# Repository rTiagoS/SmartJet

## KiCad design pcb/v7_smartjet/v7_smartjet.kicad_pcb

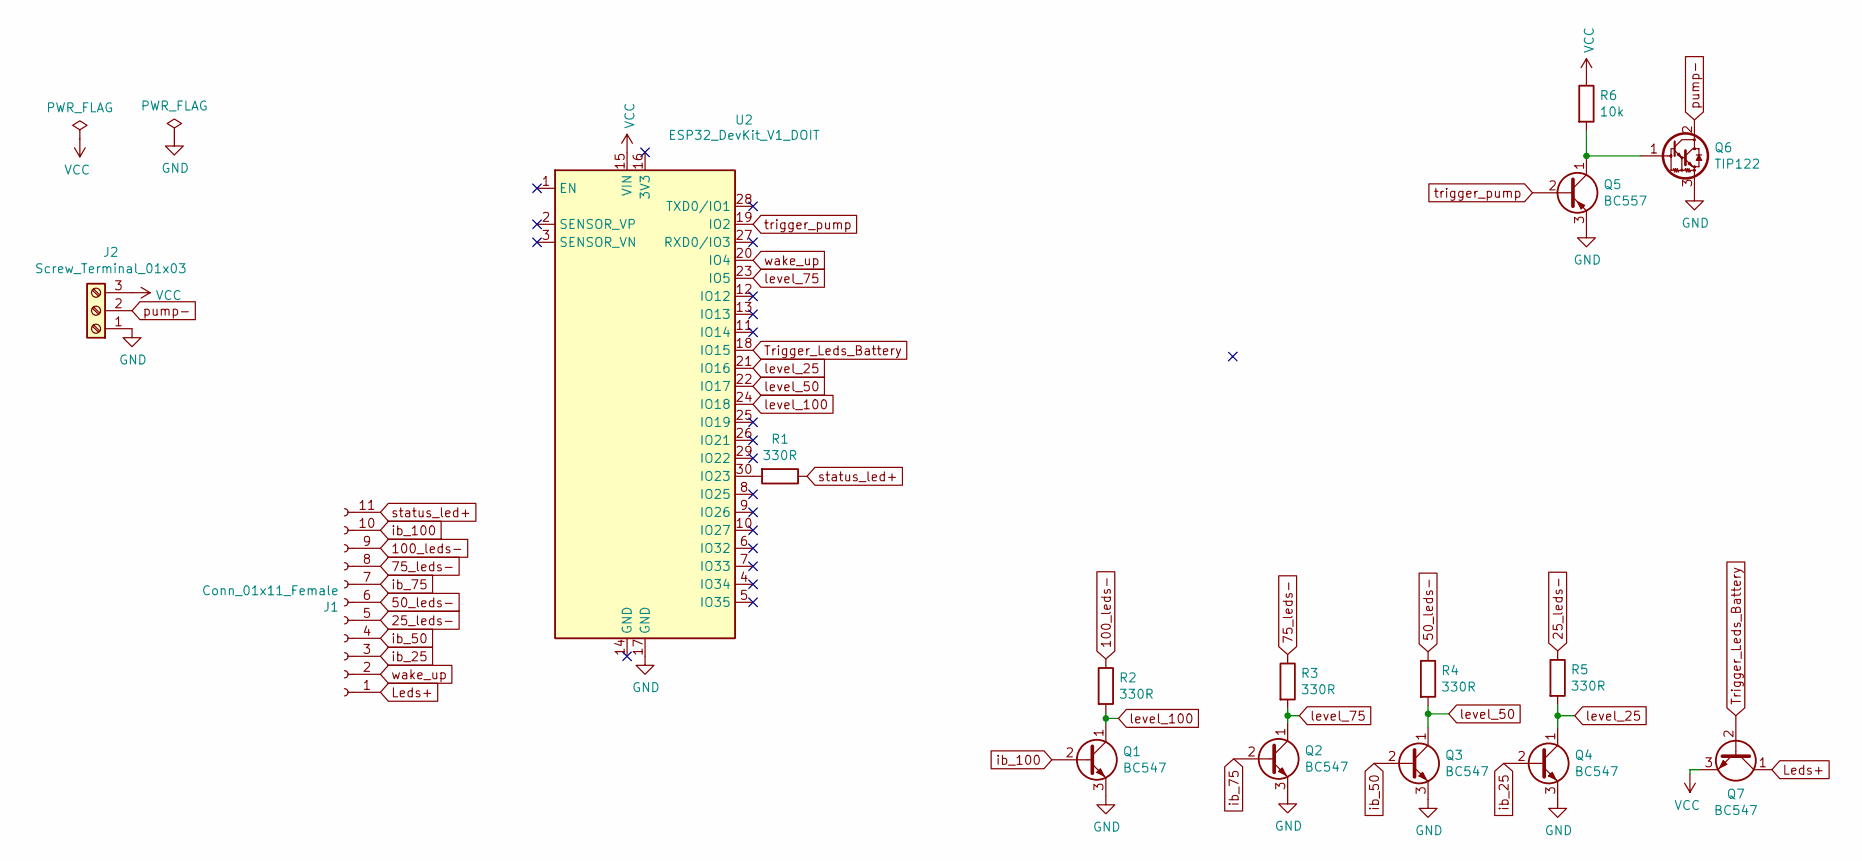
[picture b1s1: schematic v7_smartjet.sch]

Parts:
J1: Conn_01x11_Female; PinSocket_1x11_P2.54mm_Horizontal
J2: Screw_Terminal_01x03; TerminalBlock_bornier-3_P5.08mm
Q1, Q2, Q3, Q4, Q7: BC547; TO-92_Inline
Q5: BC557; TO-92_Inline
Q6: TIP122; TO-220-3_Vertical
R1, R2, R3, R4, R5: 330R; R_Axial_DIN0204_L3.6mm_D1.6mm_P7.62mm_Horizontal
R6: 10k; R_Axial_DIN0204_L3.6mm_D1.6mm_P7.62mm_Horizontal
U2: ESP32_DevKit_V1_DOIT; esp32_devkit_v1

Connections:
25_leds-: J1.5, R5.1
50_leds-: J1.6, R4.1
75_leds-: J1.8, R3.1
100_leds-: J1.9, R2.1
GND: J2.1, Q1.3 (E), Q2.3 (E), Q3.3 (E), Q4.3 (E), Q5.3 (E), Q6.3 (E), U2.17 (GND)
Leds+: J1.1, Q7.1 (C)
unnamed: Q5.1 (C), Q6.1 (B), R6.2
unnamed: R1.2, U2.30 (IO23)
Trigger_Leds_Battery: Q7.2 (B), U2.18 (IO15)
VCC: J2.3, Q7.3 (E), R6.1, U2.15 (VIN)
ib_25: J1.3, Q4.2 (B)
ib_50: J1.4, Q3.2 (B)
ib_75: J1.7, Q2.2 (B)
ib_100: J1.10, Q1.2 (B)
level_25: Q4.1 (C), R5.2, U2.21 (IO16)
level_50: Q3.1 (C), R4.2, U2.22 (IO17)
level_75: Q2.1 (C), R3.2, U2.23 (IO5)
level_100: Q1.1 (C), R2.2, U2.24 (IO18)
pump-: J2.2, Q6.2 (C)
status_led+: J1.11, R1.1
trigger_pump: Q5.2 (B), U2.19 (IO2)
wake_up: J1.2, U2.20 (IO4)

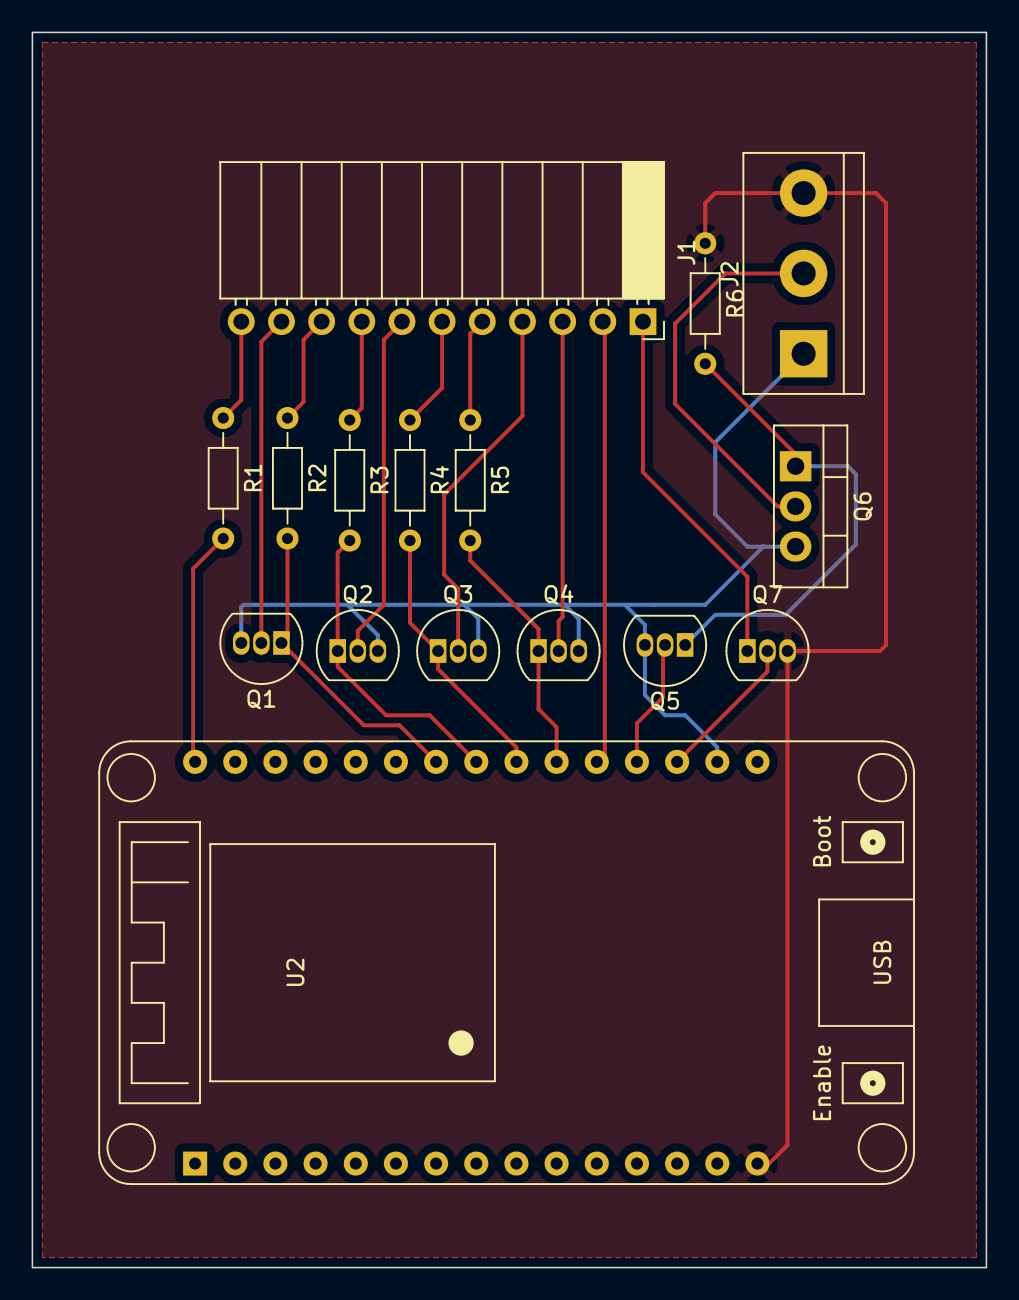
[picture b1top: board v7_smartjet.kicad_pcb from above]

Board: 2 copper layers, 60.3 x 78.1 mm, 16 parts (0 on the bottom side), 22 nets.

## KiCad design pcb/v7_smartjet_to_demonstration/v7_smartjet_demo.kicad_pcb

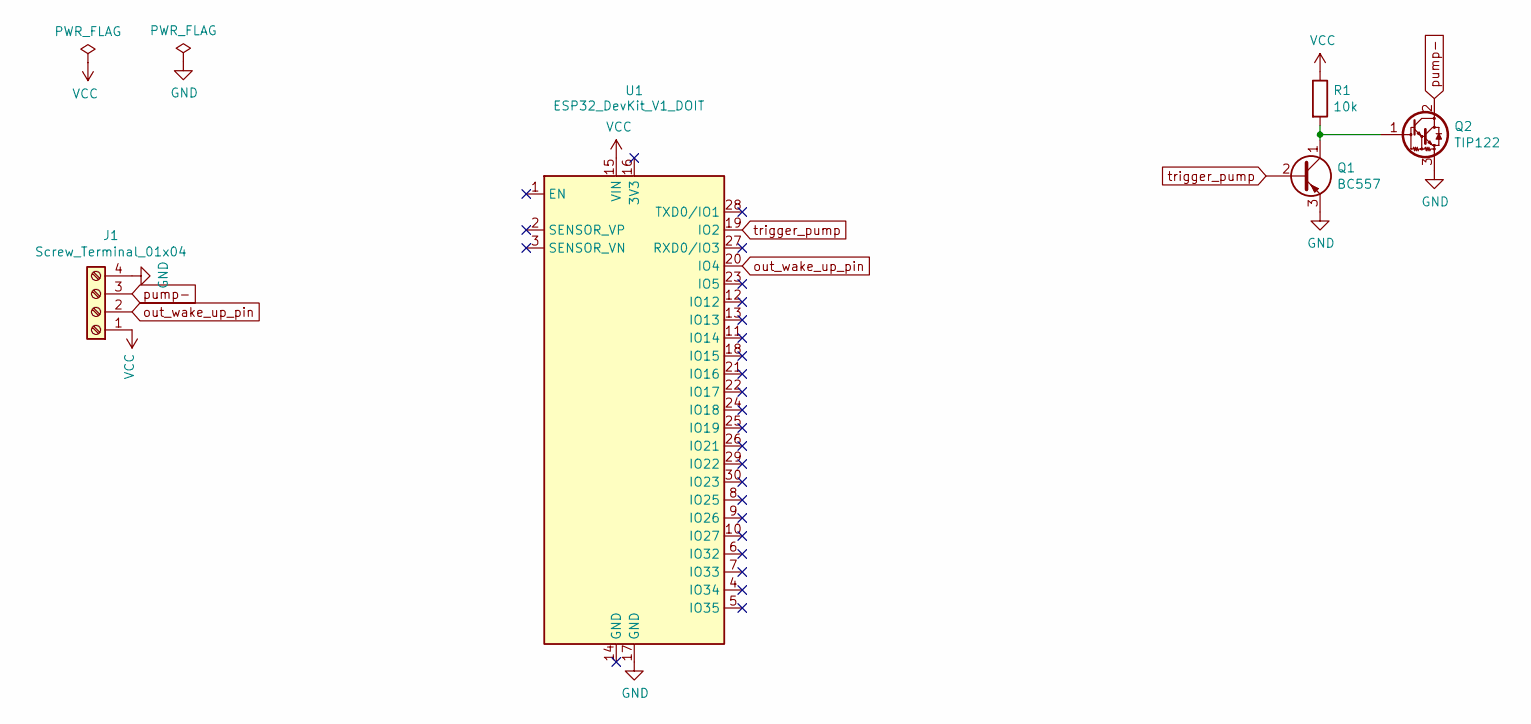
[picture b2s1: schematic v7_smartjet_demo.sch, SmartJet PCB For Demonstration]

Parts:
J1: Screw_Terminal_01x04; TerminalBlock_bornier-4_P5.08mm
Q1: BC557; TO-92_Inline
Q2: TIP122; TO-220-3_Vertical
R1: 10k; R_Axial_DIN0204_L3.6mm_D1.6mm_P7.62mm_Horizontal
U1: ESP32_DevKit_V1_DOIT; esp32_devkit_v1

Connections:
GND: J1.4, Q1.3 (E), Q2.3 (E), U1.17 (GND)
unnamed: Q1.1 (C), Q2.1 (B), R1.2
VCC: J1.1, R1.1, U1.15 (VIN)
out_wake_up_pin: J1.2, U1.20 (IO4)
pump-: J1.3, Q2.2 (C)
trigger_pump: Q1.2 (B), U1.19 (IO2)

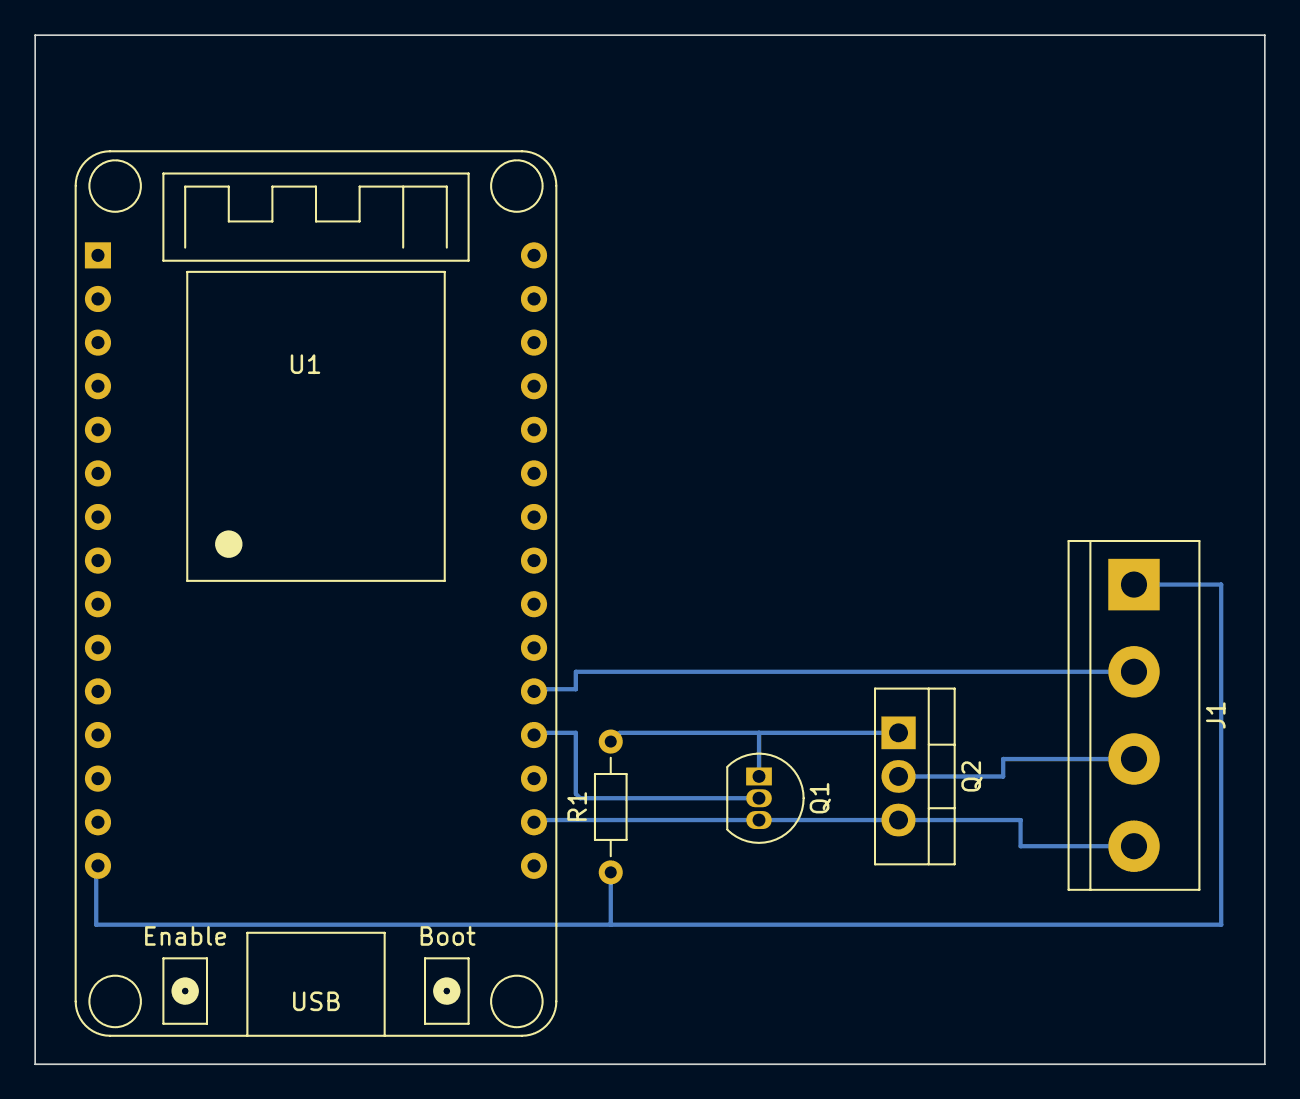
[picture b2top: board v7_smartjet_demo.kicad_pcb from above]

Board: 2 copper layers, 71.6 x 59.9 mm, 5 parts (0 on the bottom side), 6 nets.

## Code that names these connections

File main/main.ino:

#include "SmartJet.h"

#define DEBUG
#ifdef DEBUG
#define DEBUG_PRINTLN(x) Serial.println(x)
#define DEBUG_PRINT(x) Serial.print(x)
#else
#define DEBUG_PRINTLN(x)
#define DEBUG_PRINT(x)
#endif


struct smartjet_data  eeprom;

void setup()
{
  Serial.begin(115200);
  delay(1000); // Take some time to open up the Serial Monitor

  DEBUG_PRINTLN("\n***** ESP32 Waking Up: Setup Initialization *****\n");
  

  print_wakeup_reason(); // Print the wakeup reason for ESP32

  /* = = = Pinout Initialization Settings = = = */
  pinMode(pump_pin , OUTPUT); // Pump pin
  pinMode(WAKE_UP_PIN, INPUT); // Pin that provides the wake up: obstacle sensor
  //pinMode(LEVEL_LEDS_PIN, OUTPUT); // Pin to activate the levels indicator 
  //pinMode(level_100, INPUT_PULLUP);
  //pinMode(level_75, INPUT_PULLUP);
  //pinMode(level_50, INPUT_PULLUP);
  //pinMode(level_25, INPUT_PULLUP);
  

  digitalWrite(LEVEL_LEDS_PIN, LOW);
  digitalWrite(pump_pin, LOW); // Pump starts off.
  /* = = = = = = = = = = = = = = = = = = = = = = */

  /* = = = READ DATA STRUCT FROM EEPROM = = = */
  read_data(&eeprom);
  
  /* - - - - - - - - - - - - - - - - - - - - - */

  
  is_first_time = (strlen(eeprom.ssid) == 0); // Return true if the EEPROM is empty. 


  
  if (is_first_time)
  {
    /* = = = FIRST TIME CONDITION: REGISTER THE SMARTJETS = = = */
    
    connect_result = connect_to_smartjet_AP(); // Try to connect to a smartjet device (master) in order to get the credentials.

    
    if (connect_result == true)
    {
      /* = = = SMARTJETS ACTING LIKE A SLAVE = = = */
      
      String payload = http_request_json_data("http://192.168.4.1/user_credentials"); // Try to request user credentials (stuffs about Wi-Fi credentials).

      
      if (request_result == true)
      {
        
        deserialize_http_payload(payload); // Update the eeprom struct before check if the data provided are really correct.
        
        // Save the data provided by the content payload into EEPROM only after validate the data.
        save_smarjet_struct_data(&eeprom);
        
        rtc_reset_count(); // Reset parameters count at the first time
        firebase_update_parameters(); // Create a firebase directory for the first time
        
        ESP.restart(); // Restart. Then the smartjet start to work normally.
      }
    }
    else
    {
      /* = = = SMARTJETS ACTING LIKE A MASTER = = = */
      
      /* - - - Web Services Initializatiion - - - */ 
      initialize_wifi_as_ap(); // Initialize the smartjet (master) Wi-Fi  as Access Point     
      initialize_web_server(); //  It starts to listen for incoming posts requests. (Async Web Server)
      
      DEBUG_PRINT("Waiting for a Post Request");

      /*  while the number of smartjets to be registered has not been reached yet, loop. */
      while (is_first_time != false)
      {
        
        DEBUG_PRINT(".");
        delay(500);   
      }
      
      bool save_result{false};
      save_result = save_smarjet_struct_data(&eeprom);
      if (save_result == true)
      {
        rtc_reset_count(); // Reset parameters count at the first time.
        firebase_update_parameters(); // Create directories on RTDB. It's the first publish.
        handle_get_requests(); // Now it can answer for incoming get requests.
      }
      else
      {
        DEBUG_PRINTLN(" Please, confirm the credentials informed and try again. ");
        Serial.print("\n Rebooting ESP...");
        ESP.restart();
      }
    }
  }

    
  else
  {
    /* = = = REACH HERE WHEN THE SMARTJET IS ALREADY REGISTERED = = = */
    
    trigger_pump(); // Every wake up from deep sleep, the smartjet striggers gel
    
    //show_indicator_level_leds(); // NOT USED -> NO BATTERIES WILL BE USED

    //get_liquid_level();          // IT WILL BE USED WHEN SOLVE A CONSISTENT WAY TO MEASURE THE LEVEL.

    update_RTC_dispenser_parameters(); // Update the dispenser parameters at RTC memory
   

    if (is_time_publish()) // Conditions to publish: for each 5 triggers.
    {
      initialize_wifi_as_client(); // Turn on the Wi-Fi connection
      
      firebase_check_for_delete(); // Check into firebase if the user decided for deleting this smartjet.
      
      /* - - - Internet Settings - - - */
      firebase_update_parameters(); // Update the dashboard app.
      /* - - - - - - - - - - - - - - - */
      if (is_time_to_notifications()) // Conditions to push notifications: low battery level or low liquid level
      {
        //search_for_id_player();
        push_notification("Warning!!!: SmartJet Low Level\nPlease, before another use, you must recharge it!");
      }
    }
    
    delay(700);
    
    factory_reset(); // Check for user request to reset the Smart Jet from factory. 
    
    go_light_sleep(); // Actually, it is deep sleep, not light sleep mode.
  }
}
void loop()
{
}

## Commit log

2021-01-15 Adicionando arquivo .gitignore
2021-01-15 Adicionando diretório do desenvolvimento do código a ser monitorado.
2021-01-15 Implementação de funções para se adequar à nova solicitação de mensagens em formato Json em apenas um único tópico. Implementações anteriores foram deletadas.
2021-01-16 Implementado rota para salvar email do usuário na memória EEPROM.
2021-01-16 Alterado os parâmetros da função publishBuffer. Agora são enviados os Jets e Nível do Líquido.
2021-01-19 1. Adicionado nova rota para responde a uma request via método POST das credenciais do usuário. 2. Modificado nome de variáveis para ficar mais legível o código. 3. Criado dois tópicos do Broker: um 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
2021-01-20 1. Alterado função para responder a requisição do Slave com mais uma informação: o email do usuário. 2. Elaborado o código para as mesmas funcionalidades do Master, porém no slave com algumas diferen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
2021-02-08 Código implementado com as seguintes otimizações: 1. Uso da bateria ( modo deep sleep). 2 Centralização das aplicações em apenas um servidor de banco de dados - Firebase.
